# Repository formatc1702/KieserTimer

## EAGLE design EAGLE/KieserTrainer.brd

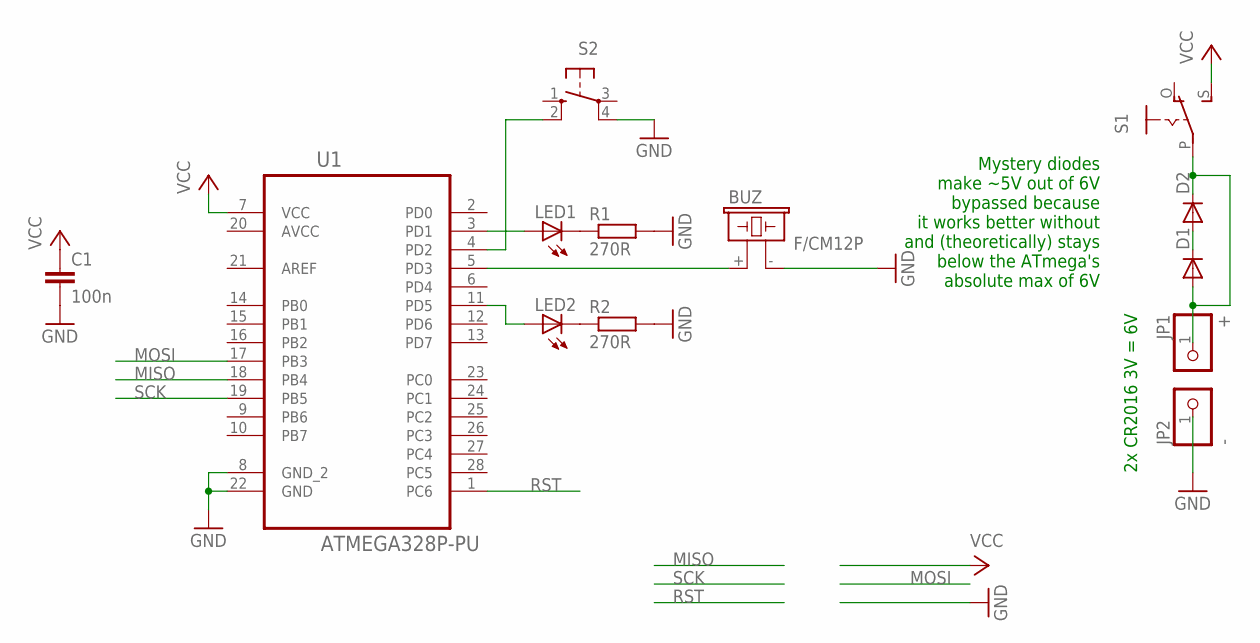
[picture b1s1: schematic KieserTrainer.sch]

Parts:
BUZ: F/CM12P
C1: 100n; C0805
D1, D2: DIODE-D-7.5; D-7.5
JP1: +; 1X01
JP2: -; 1X01
LED1, LED2: LED3MM
R1, R2: 270R; R0805
S1: EG1218S; EG1218
S2: 10-XX; B3F-10XX
U1: ATMEGA328P-PU; DIP254P762X457-28

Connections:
AVCC: U1.20 (AVCC)
GND: BUZ.- (2), C1.2, JP2.1, R1.2, R2.2, S2.4 (P1), U1.8 (GND_2), U1.22 (GND)
MISO: U1.18 (PB4)
MOSI: U1.17 (PB3)
unnamed: LED1.K (C), R1.1
unnamed: LED2.K (C), R2.1
unnamed: LED1.A, U1.3 (PD1)
unnamed: LED2.A, U1.11 (PD5)
unnamed: BUZ.+ (1), U1.5 (PD3)
unnamed: D1.A, D2.C, JP1.1, S1.P
unnamed: S2.2 (S1), U1.4 (PD2)
unnamed: D1.C, D2.A
RST: U1.1 (PC6)
SCK: U1.19 (PB5)
VCC: C1.1, S1.S, U1.7 (VCC)

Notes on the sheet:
Mystery diodes make ~5V out of 6V bypassed because it works better without and (theoretically) stays below the ATmega's absolute max of 6V
2x CR2016 3V = 6V

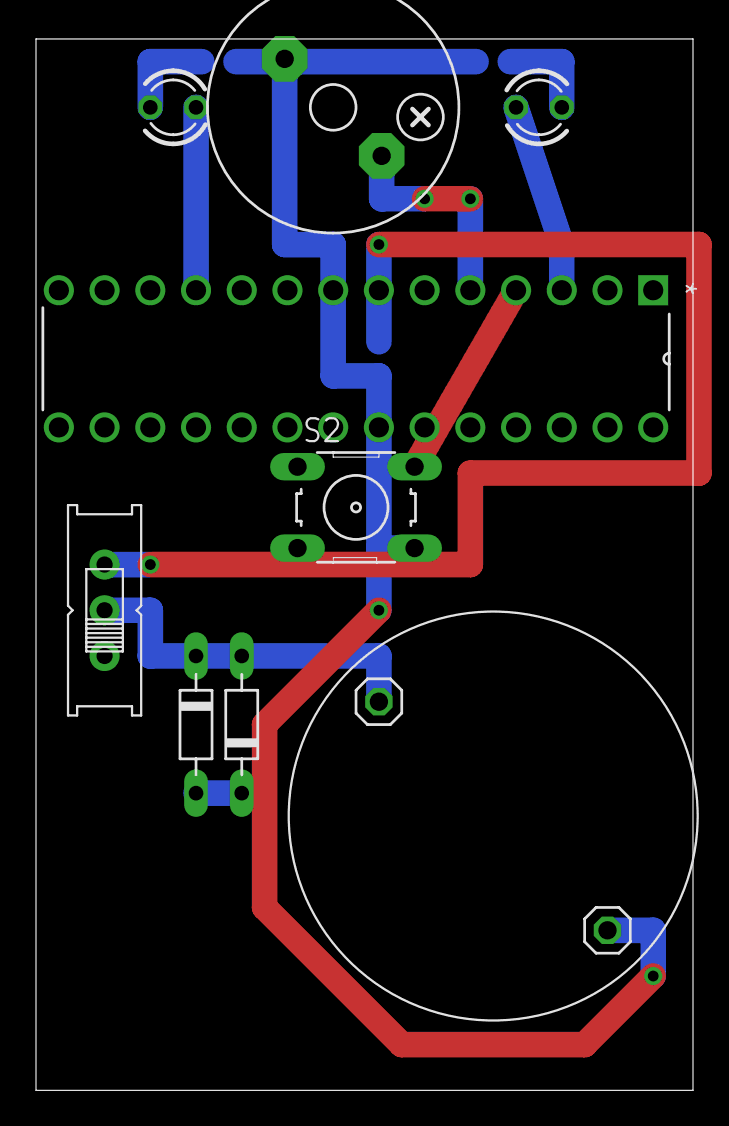
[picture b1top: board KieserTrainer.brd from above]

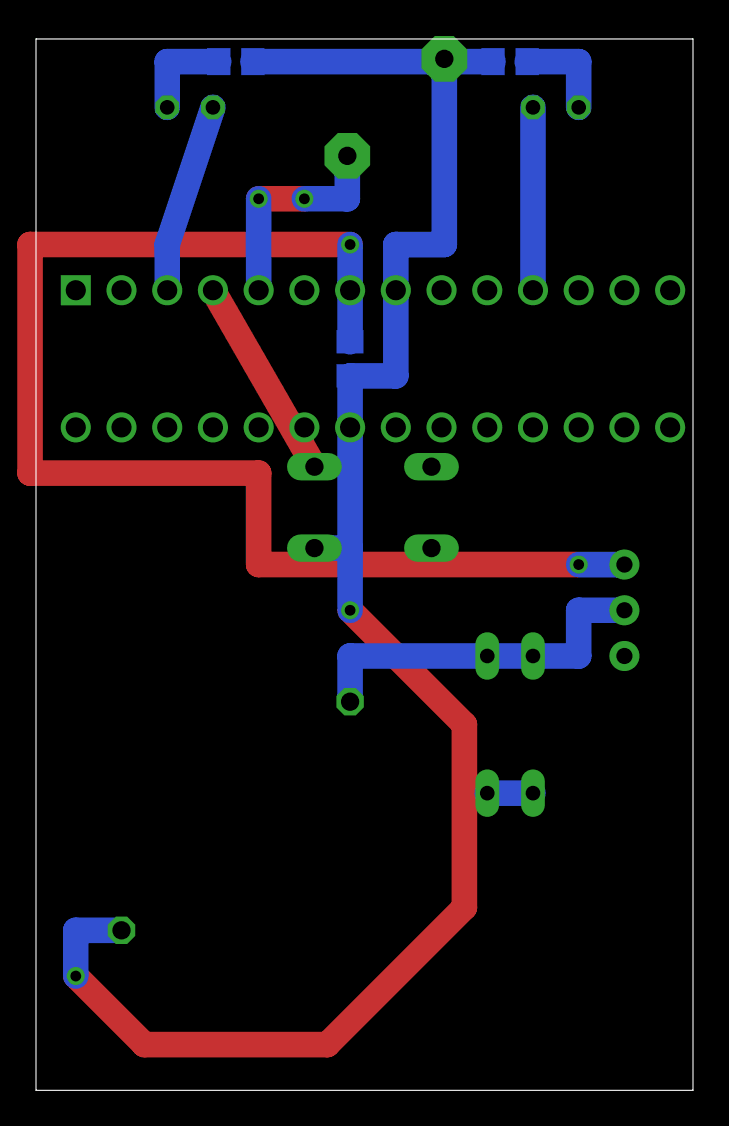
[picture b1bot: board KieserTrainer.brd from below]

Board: 2 copper layers, 36.5 x 58.4 mm, 13 parts (3 on the bottom side), 10 nets.

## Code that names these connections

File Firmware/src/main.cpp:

#include <Arduino.h>

#include "LowPower.h"

#define PIN_LED_LEFT   1 // PD1, pin  3
#define PIN_PUSHBUTTON 2 // PD2, pin  4
#define PIN_BUZZER     3 // PD3, pin  5
#define PIN_LED_RIGHT  5 // PD5, pin 11

#define TIME_GO_UP     SLEEP_4S // 4000
#define TIME_WAIT_UP   SLEEP_2S // 2250
#define TIME_GO_DOWN   SLEEP_4S // 4000
#define TIME_WAIT_DOWN SLEEP_2S // 2250

#define E5  659
#define C6 1046
#define E6 1318
#define G6 1568
#define A6 1760
#define B6 1975
#define C7 2093
#define D7 2349
#define E7 2637
#define F7 2794
#define G7 3136
#define C8 4186

#define FREQ_COUTDOWN  E6
#define FREQ_DOWN      B6
#define FREQ_UP        C7
#define FREQ_FINISHED  D7

#define NUM_REPETITIONS 10

#define DELAY_BLIP 50

int use_buzzer = 0;

void tone_delay(int pin, unsigned int freq, unsigned long duration) {
  if (use_buzzer)
    tone(pin, freq, duration);
  delay(duration);
}

void blip(int pin, int times, int duration, unsigned int freq) {
  if (freq > 0)
    if(use_buzzer)
      tone(PIN_BUZZER, freq, duration);
  for (int i = 0; i < times; i++) {
    digitalWrite(pin,HIGH);
    delay(duration);
    digitalWrite(pin,LOW);
    delay(duration);
  }
}

void blip(int pin, int times, unsigned int freq) {
  blip(pin, times, DELAY_BLIP, freq);
}

void sigCountDown() {
  blip(PIN_LED_LEFT, 1, FREQ_COUTDOWN);
}

void sigCountDownSilent() {
  blip(PIN_LED_LEFT, 1, 0);
}

void sigGoUp() {
  blip(PIN_LED_RIGHT, 1, FREQ_DOWN);
  blip(PIN_LED_RIGHT, 1, FREQ_UP);
}

void sigGoDown() {
  blip(PIN_LED_LEFT, 1, FREQ_UP);
  blip(PIN_LED_LEFT, 1, FREQ_DOWN);
}

void sigWaitUp() {
  blip(PIN_LED_RIGHT, 1, FREQ_UP);
}

void sigWaitDown() {
  blip(PIN_LED_LEFT, 1, FREQ_DOWN);
}

void sigFinished() {
  blip(PIN_LED_RIGHT, 1, 500, FREQ_FINISHED);
}

void sleep(period_t duration) {
  LowPower.powerDown(duration, ADC_OFF, BOD_OFF);
}

void isr() {}

void setup() {
  pinMode(PIN_BUZZER,OUTPUT);
  pinMode(PIN_LED_LEFT,OUTPUT);
  pinMode(PIN_LED_RIGHT,OUTPUT);
  pinMode(PIN_PUSHBUTTON,INPUT_PULLUP);
  if(digitalRead(PIN_PUSHBUTTON) == LOW)
    use_buzzer = false;
  else
    use_buzzer = true;
  digitalWrite(PIN_LED_LEFT,  HIGH);
  digitalWrite(PIN_LED_RIGHT, HIGH);
  if (use_buzzer)
    tone(PIN_BUZZER, E5, 50);
  delay(50);
  digitalWrite(PIN_LED_LEFT,  LOW);
  digitalWrite(PIN_LED_RIGHT, LOW);
}

void loop() {
  // wait 1s
  sleep(SLEEP_1S);
  // count down from 5
  for (size_t i = 0; i < 5; i++) {
    if (i < 2)
      sigCountDownSilent();
    else
      sigCountDown();
   sleep(SLEEP_1S);
  }
  // do N repetitions
  for (int i = 0; i < NUM_REPETITIONS; i++) {
    sigGoUp();      sleep(TIME_GO_UP);
    sigWaitUp();    sleep(TIME_WAIT_UP);
    sigGoDown();    sleep(TIME_GO_DOWN);
    sigWaitDown();  sleep(TIME_WAIT_DOWN);
  }
  // finished!
  sigFinished();
  // prepare for deep sleep
  attachInterrupt(digitalPinToInterrupt(PIN_PUSHBUTTON), isr, CHANGE);
  sleep(SLEEP_FOREVER);
  detachInterrupt(digitalPinToInterrupt(PIN_PUSHBUTTON));
}

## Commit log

2017-01-07 Add some PlatformIO files
2017-01-07 First working proof of concept
2017-01-07 Add countdown at startup and indication at end
2017-01-07 Implement low power sleep mode
2017-01-14 Add beeping
2017-01-14 First EAGLE design
2017-01-27 Change pins to match PCB
2017-01-27 Update schematic to match PCB
2017-01-27 Make both LEDs blue high-power (brighter!), add 2x mystery diode to make ~5V out of ~6V
2017-01-27 Add 2s delay before countdown
2017-01-27 Add bypass capactior on uC supply pins
2017-01-27 Changed labels of LED pins (red/green -> left/right)
2017-01-27 Change parameter variable type of sleep() to period_t to avoid compiler warnings
2017-01-27 Add board layout to match physical design
2017-02-14 Add musical notes, make ‘go’ and ‘wait’ signals less ambiguous
2017-02-14 Change project name ;-)
2017-02-14 Bypass mystery diodes to feed ATmega with full 6V (exactly the max rating, but oh well)
2017-02-27 Make first 3 countdown blips silent, only beep the last two
2017-03-05 Add SolveSpace mechanical CAD model
2017-03-08 Add been/no beep feature, implement hardware interrupt for waking, rewire push button and LED
